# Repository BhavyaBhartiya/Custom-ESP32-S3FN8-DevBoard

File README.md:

# Custom-ESP32-S3FN8-DevBoard
This is a custom ESP32-S3 board made on the ESP32-S3FN8 SOC with inbuilt I2C OLED display and AHT20 temperature and Humidity Sensor.

# 3D View of PCB

# PCB

# Schematic

# Render of PCB Case

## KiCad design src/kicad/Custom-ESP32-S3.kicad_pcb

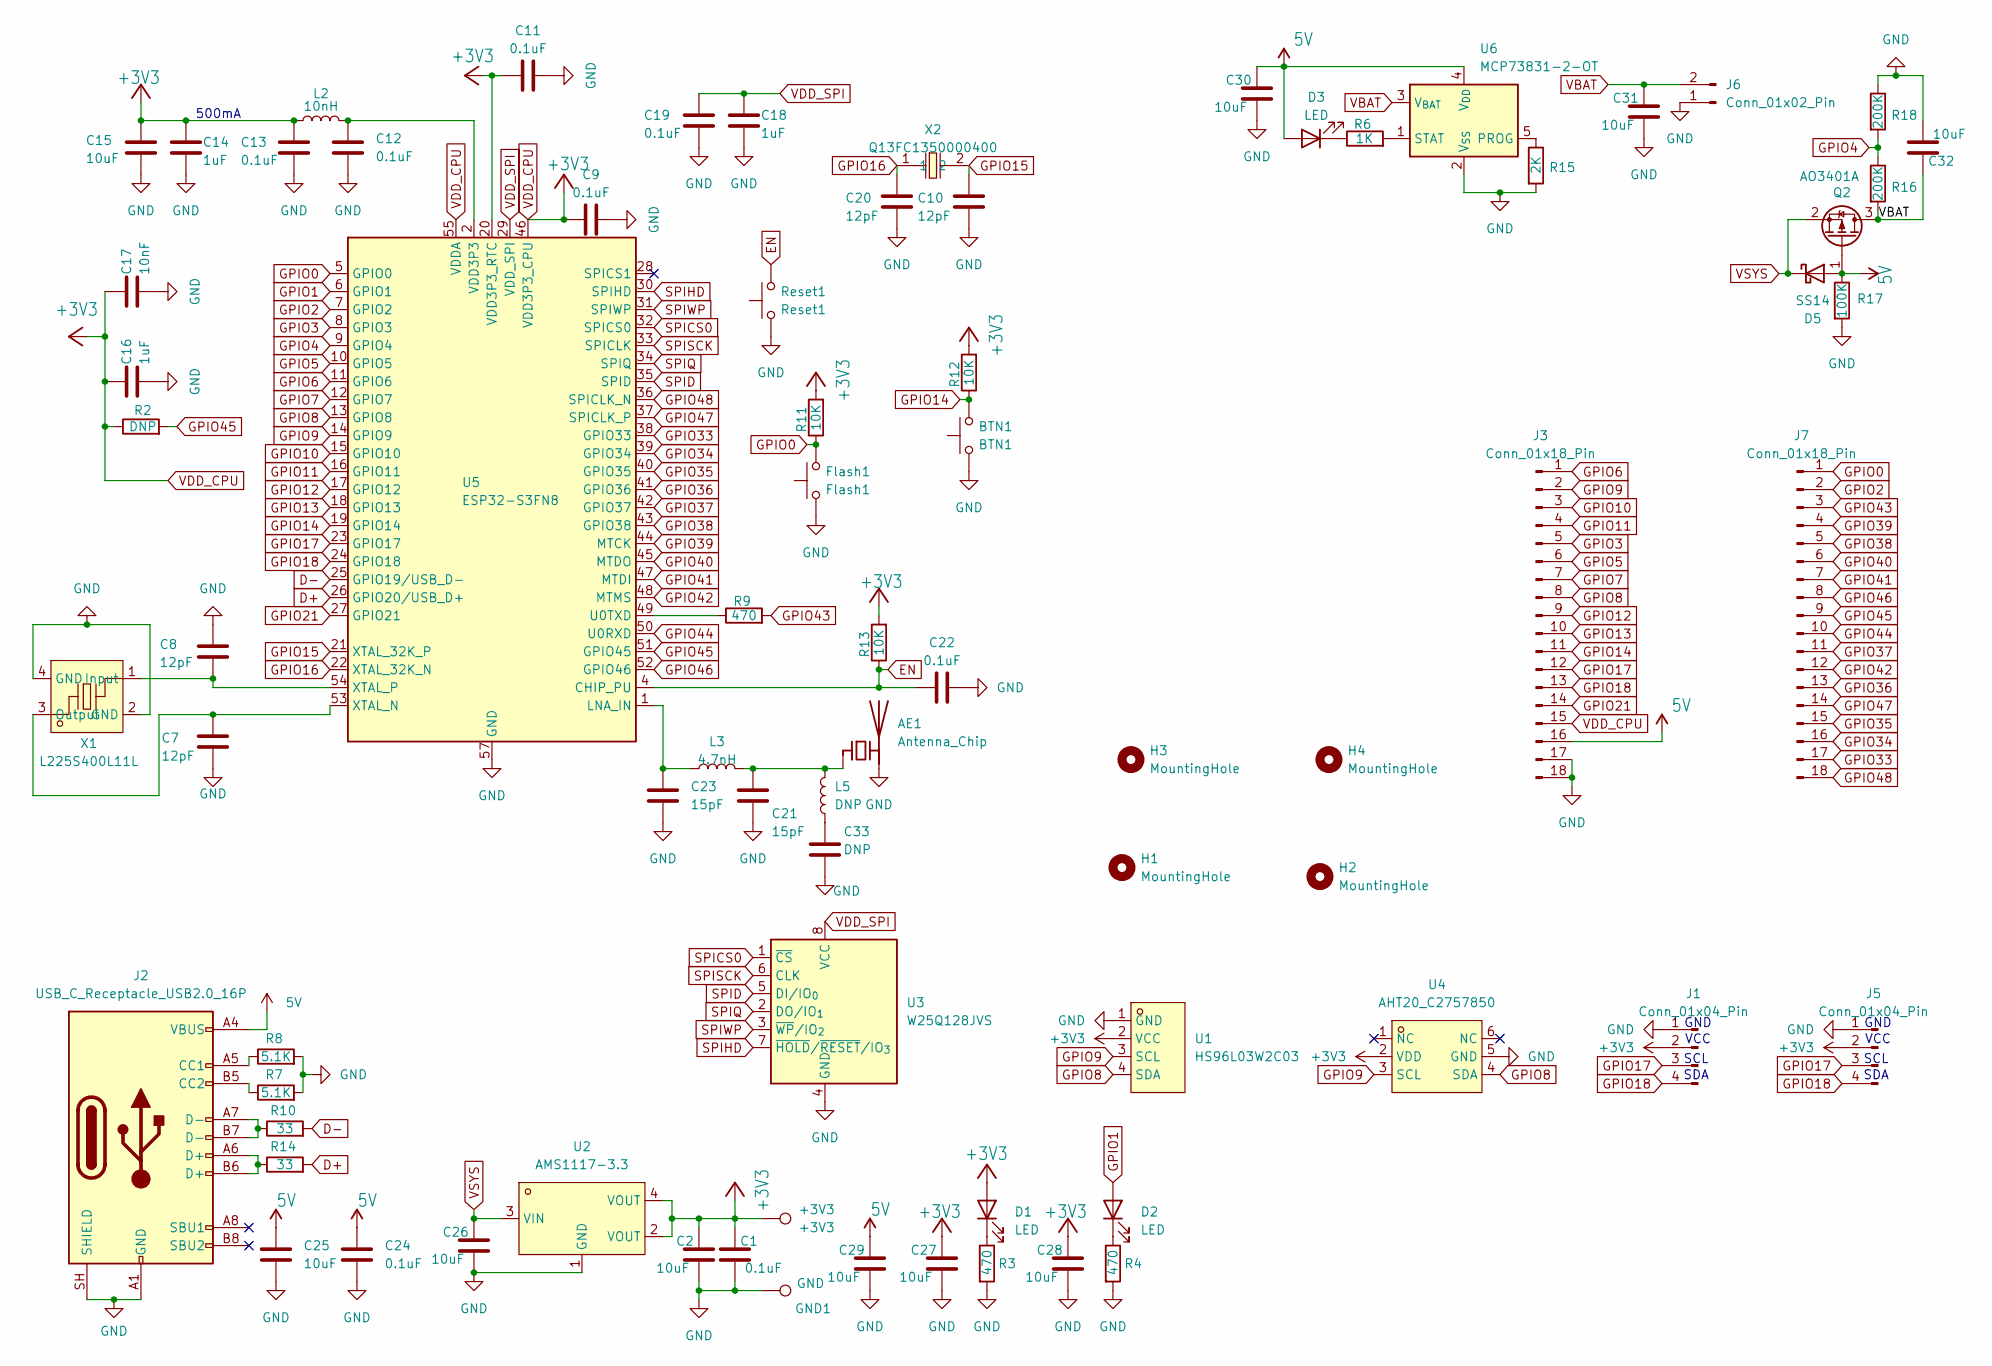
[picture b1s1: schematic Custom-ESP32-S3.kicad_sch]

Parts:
+3V3: +3V3; TestPoint_Pad_D1.0mm
AE1: Antenna_Chip; Texas_SWRA117D_2.4GHz_Left
BTN1: BTN1; SW_Push_1P1T_XKB_TS-1187A; LCSC Part C318884
C1, C9, C11, C12, C13, C19, C22, C24: 0.1uF; C_0402_1005Metric; LCSC Part C1525
C2, C15, C25, C26, C27, C28, C29, C30, C31, C32: 10uF; C_0402_1005Metric; LCSC Part C15525
C7, C8, C10, C20: 12pF; C_0402_1005Metric; LCSC Part C1547
C14, C16, C18: 1uF; C_0402_1005Metric; LCSC Part C52923
C17: 10nF; C_0402_1005Metric; LCSC Part C15195
C21, C23: 15pF; C_0402_1005Metric; LCSC Part C1548
C33: DNP; C_0402_1005Metric
D1, D2, D3: LED; LED_0603_1608Metric; LCSC Part C2286
D5: SS14; D_SMA; LCSC Part C2480
Flash1: Flash1; SW_Push_1P1T_XKB_TS-1187A; LCSC Part C318884
GND1: GND; TestPoint_Pad_D1.0mm
H1, H2, H3, H4: MountingHole; MountingHole_2.1mm
J1, J5: Conn_01x04_Pin; PinHeader_1x04_P2.54mm_Vertical
J2: USB_C_Receptacle_USB2.0_16P; USB-C-SMD_TYPE-C-16PIN-2MD-073; LCSC Part C19274016
J3, J7: Conn_01x18_Pin; PinHeader_1x18_P2.54mm_Vertical
J6: Conn_01x02_Pin; PinSocket_1x02_P2.54mm_Vertical
L2: 10nH; L_0402_1005Metric; LCSC Part C77103
L3: 4.7nH; L_0402_1005Metric; LCSC Part C13595
L5: DNP; L_0402_1005Metric
Q2: AO3401A; SOT-23; LCSC Part C15127
R2: DNP; R_0402_1005Metric
R3, R4, R9: 470; R_0402_1005Metric; LCSC Part C25117
R6: 1K; R_0402_1005Metric; LCSC Part C11702
R7, R8: 5.1K; R_0402_1005Metric; LCSC Part C25905
R10, R14: 33; R_0402_1005Metric; LCSC Part C25105
R11, R12, R13: 10K; R_0402_1005Metric; LCSC Part C25744
R15: 2K; R_0402_1005Metric; LCSC Part C4109
R16, R18: 200K; R_0402_1005Metric; LCSC Part C25764
R17: 100K; R_0402_1005Metric; LCSC Part C25741
Reset1: Reset1; SW_Push_1P1T_XKB_TS-1187A; LCSC Part C318884
U1: HS96L03W2C03; OLED-TH_L27.8-W27.2-P2.54_C9900033791; MPN HS96L03W2C03; LCSC Part C5248080
U2: AMS1117-3.3; SOT-223-3_L6.5-W3.4-P2.30-LS7.0-BR; MPN AMS1117-3.3; LCSC Part C6186
U3: W25Q128JVS; SOIC-8_5.3x5.3mm_P1.27mm; LCSC Part C97521
U4: AHT20_C2757850; SENSOR-SMD_L3.0-W3.0-P1.00-BR; MPN AHT20; LCSC Part C2757850
U5: ESP32-S3FN8; QFN-56-1EP_7x7mm_P0.4mm_EP4x4mm; LCSC Part C2913196
U6: MCP73831-2-OT; SOT-23-5; LCSC Part C296277
X1: L225S400L11L; CRYSTAL-SMD_4P-L2.5-W2.0-BL-1; MPN L225S400L11L; LCSC Part C5261125
X2: Q13FC1350000400; FC-135R_L3.2-W1.5; MPN Q13FC13500004; LCSC Part C32346

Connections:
5V: C24.1, C25.1, C29.1, C30.1, D3.2 (A), D5.2 (A), J2.A4 (VBUS), J2.A9 (VBUS), J2.B4 (VBUS), J2.B9 (VBUS), J3.16, Q2.1 (G), R17.1, U6.4 (V_{DD})
D+: R14.2, U5.26 (GPIO20/USB_D+)
D-: R10.2, U5.25 (GPIO19/USB_D-)
EN: C22.1, R13.1, Reset1.2, U5.4 (CHIP_PU)
GND: AE1.2 (PCB_Trace), BTN1.1, C1.2, C2.2, C7.2, C8.1, C9.1, C10.2, C11.1, C12.1, C13.1, C14.1, C15.2, C16.1, C17.1, C18.1, C19.1, C20.2, C21.2, C22.2, C23.2, C24.2, C25.2, C26.2, C27.2, C28.2, C29.2, C30.2, C31.2, C32.2, C33.2, Flash1.1, GND1.1 (1_1), J1.1, J2.A1 (GND), J2.A12 (GND), J2.B1 (GND), J2.B12 (GND), J2.SH (SHIELD), J3.17, J3.18, J5.1, J6.1, R3.2, R4.2, R7.2, R8.2, R15.2, R17.2, R18.1, Reset1.1, U1.1 (GND), U2.1 (GND), U3.4 (GND), U4.5 (GND), U5.57 (GND), U6.2 (V_{SS}), X1.2 (GND), X1.4 (GND)
GPIO0: Flash1.2, J7.1, R11.1, U5.5 (GPIO0)
GPIO1: D2.2 (A), U5.6 (GPIO1)
GPIO2: J7.2, U5.7 (GPIO2)
GPIO3: J3.5, U5.8 (GPIO3)
GPIO4: R16.1, R18.2, U5.9 (GPIO4)
GPIO5: J3.6, U5.10 (GPIO5)
GPIO6: J3.1, U5.11 (GPIO6)
GPIO7: J3.7, U5.12 (GPIO7)
GPIO8: J3.8, U1.4 (SDA), U4.4 (SDA), U5.13 (GPIO8)
GPIO9: J3.2, U1.3 (SCL), U4.3 (SCL), U5.14 (GPIO9)
GPIO10: J3.3, U5.15 (GPIO10)
GPIO11: J3.4, U5.16 (GPIO11)
GPIO12: J3.9, U5.17 (GPIO12)
GPIO13: J3.10, U5.18 (GPIO13)
GPIO14: BTN1.2, J3.11, R12.1, U5.19 (GPIO14)
GPIO15: C10.1, U5.21 (XTAL_32K_P), X2.2
GPIO16: C20.1, U5.22 (XTAL_32K_N), X2.1
GPIO17: J1.3, J3.12, J5.3, U5.23 (GPIO17)
GPIO18: J1.4, J3.13, J5.4, U5.24 (GPIO18)
GPIO21: J3.14, U5.27 (GPIO21)
GPIO33: J7.17, U5.38 (GPIO33)
GPIO34: J7.16, U5.39 (GPIO34)
GPIO35: J7.15, U5.40 (GPIO35)
GPIO36: J7.13, U5.41 (GPIO36)
GPIO37: J7.11, U5.42 (GPIO37)
GPIO38: J7.5, U5.43 (GPIO38)
GPIO39: J7.4, U5.44 (MTCK)
GPIO40: J7.6, U5.45 (MTDO)
GPIO41: J7.7, U5.47 (MTDI)
GPIO42: J7.12, U5.48 (MTMS)
GPIO43: J7.3, R9.2
GPIO44: J7.10, U5.50 (U0RXD)
GPIO45: J7.9, R2.2, U5.51 (GPIO45)
GPIO46: J7.8, U5.52 (GPIO46)
GPIO47: J7.14, U5.37 (SPICLK_P)
GPIO48: J7.18, U5.36 (SPICLK_N)
unnamed: AE1.1 (FEED), C21.1, L3.2, L5.2
unnamed: C12.2, L2.2, U5.2 (VDD3P3), U5.3 (VDD3P3)
unnamed: C33.1, L5.1
unnamed: D1.1 (K), R3.1
unnamed: D2.1 (K), R4.1
unnamed: D3.1 (K), R6.1
unnamed: J2.A5 (CC1), R8.1
unnamed: J2.B5 (CC2), R7.1
unnamed: J2.A6 (D+), J2.B6 (D+), R14.1
unnamed: J2.A7 (D-), J2.B7 (D-), R10.1
unnamed: C23.1, L3.1, U5.1 (LNA_IN)
unnamed: R9.1, U5.49 (U0TXD)
unnamed: C7.1, U5.53 (XTAL_N), X1.3 (Output)
unnamed: C8.2, U5.54 (XTAL_P), X1.1 (Input)
unnamed: R15.1, U6.5 (PROG)
unnamed: R6.2, U6.1 (STAT)
SPICS0: U3.1 (~CS), U5.32 (SPICS0)
SPID: U3.5 (DI/IO_{0}), U5.35 (SPID)
SPIHD: U3.7 (~HOLD/~RESET/IO_{3}), U5.30 (SPIHD)
SPIQ: U3.2 (DO/IO_{1}), U5.34 (SPIQ)
SPISCK: U3.6 (CLK), U5.33 (SPICLK)
SPIWP: U3.3 (~WP/IO_{2}), U5.31 (SPIWP)
VBAT: C31.1, C32.1, J6.2, Q2.3 (D), R16.2, U6.3 (V_{BAT})
VDD_CPU: +3V3.1 (1_1), C1.1, C2.1, C9.2, C11.2, C13.2, C14.2, C15.1, C16.2, C17.2, C27.1, C28.1, D1.2 (A), J1.2, J3.15, J5.2, L2.1, R2.1, R11.2, R12.2, R13.2, U1.2 (VCC), U2.2 (VOUT), U2.4 (VOUT), U4.2 (VDD), U5.20 (VDD3P3_RTC), U5.46 (VDD3P3_CPU), U5.55 (VDDA), U5.56 (VDDA)
VDD_SPI: C18.2, C19.2, U3.8 (VCC), U5.29 (VDD_SPI)
VSYS: C26.1, D5.1 (K), Q2.2 (S), U2.3 (VIN)

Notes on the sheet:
SCL
VCC
GND
500mA
SDA

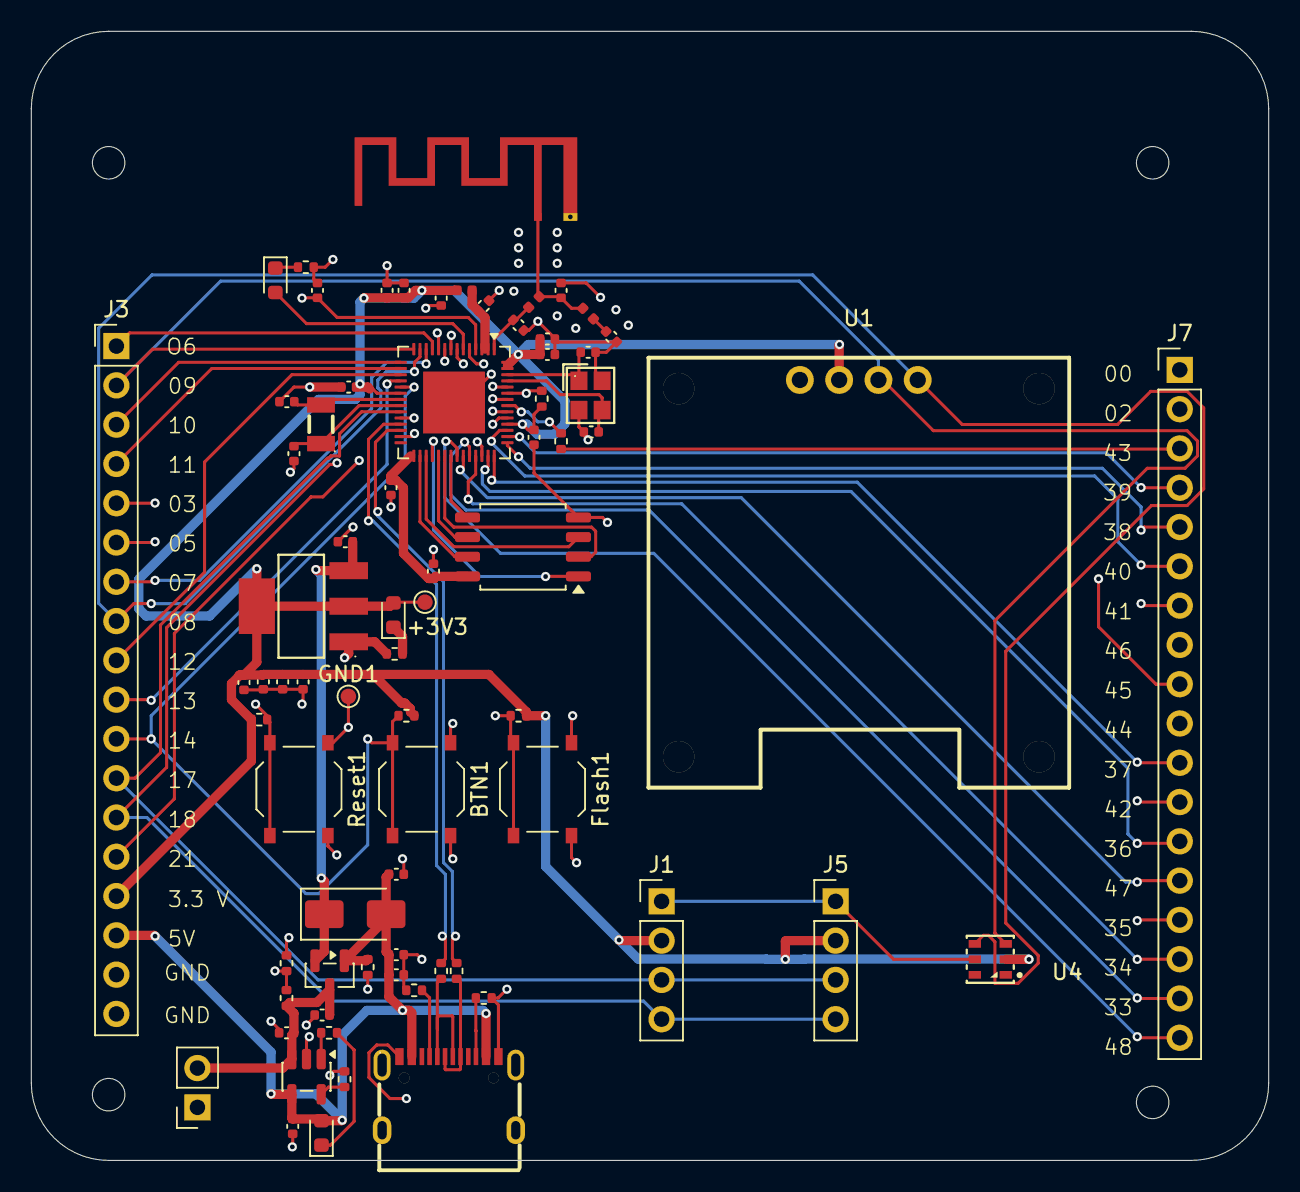
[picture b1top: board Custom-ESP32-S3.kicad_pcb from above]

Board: 4 copper layers, 80.0 x 73.0 mm, 77 parts (0 on the bottom side), 67 nets.

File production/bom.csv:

Designator,Footprint,Quantity,Value,LCSC Part #
+3V3,TestPoint_Pad_D1.0mm,1,+3V3,
AE1,Texas_SWRA117D_2.4GHz_Left,1,Antenna_Chip,
BTN1,SW_Push_1P1T_XKB_TS-1187A,1,BTN1,C318884
"C1, C11, C12, C13, C19, C22, C24, C9",0402,8,0.1uF,C1525
"C10, C20, C7, C8",0402,4,12pF,C1547
"C14, C16, C18",0402,3,1uF,C52923
"C15, C2, C25, C26, C27, C28, C29, C30, C31, C32",0402,10,10uF,C15525
C17,0402,1,10nF,C15195
"C21, C23",0402,2,15pF,C1548
"C33, L5, R2",0402,3,DNP,
"D1, D2, D3",0603,3,LED,C2286
D5,D_SMA,1,SS14,C2480
FLASH1,SW_Push_1P1T_XKB_TS-1187A,1,Flash1,C318884
GND1,TestPoint_Pad_D1.0mm,1,GND,
"H1, H2, H3, H4",MountingHole_2.1mm,4,MountingHole,
"J1, J5",PinHeader_1x04_P2.54mm_Vertical,2,Conn_01x04_Pin,
J2,USB-C-SMD_TYPE-C-16PIN-2MD-073,1,USB_C_Receptacle_USB2.0_16P,C19274016
"J3, J7",PinHeader_1x18_P2.54mm_Vertical,2,Conn_01x18_Pin,
J6,PinSocket_1x02_P2.54mm_Vertical,1,Conn_01x02_Pin,
L2,0402,1,10nH,C77103
L3,0402,1,4.7nH,C13595
Q2,SOT-23,1,AO3401A,C15127
"R10, R14",0402,2,33,C25105
"R11, R12, R13",0402,3,10K,C25744
R15,0402,1,2K,C4109
"R16, R18",0402,2,200K,C25764
R17,0402,1,100K,C25741
"R3, R4, R9",0402,3,470,C25117
R6,0402,1,1K,C11702
"R7, R8",0402,2,5.1K,C25905
RESET1,SW_Push_1P1T_XKB_TS-1187A,1,Reset1,C318884
U1,OLED-TH_L27.8-W27.2-P2.54_C9900033791,1,HS96L03W2C03,C5248080
U2,SOT-223-3_L6.5-W3.4-P2.30-LS7.0-BR,1,AMS1117-3.3,C6186
U3,SOIC-8_5.3x5.3mm_P1.27mm,1,W25Q128JVS,C97521
U4,SENSOR-SMD_L3.0-W3.0-P1.00-BR,1,AHT20_C2757850,C2757850
U5,QFN-56-1EP_7x7mm_P0.4mm_EP4x4mm,1,ESP32-S3FN8,C2913196
U6,SOT-23-5,1,MCP73831-2-OT,C296277
X1,CRYSTAL-SMD_4P-L2.5-W2.0-BL-1,1,L225S400L11L,C5261125
X2,FC-135R_L3.2-W1.5,1,Q13FC1350000400,C32346

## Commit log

2026-05-27 Add PCB case render to README
